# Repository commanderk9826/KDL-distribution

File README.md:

# Introduction

KDL(Kust Data Logger)는 대학생 자작자동차대회 출전차량을 위해 제작한 데이터로깅 플랫폼입니다. 
가이드에 따라 실시간 원격 모니터링, 데이터 분석 도구 등을 쉽게 이용할 수 있습니다.<br>

참여자 : 이채훈, 옹미령, 강호, 이지규<br>
PCB제작 : 고민제<br>
최신버전 [ui_config.json](https://github.com/commanderk9826/KDL-distribution/blob/main/ui_configKUST.json)

**주요 기능**
- CAN, 3축 가속도, GPS, 디지털/아날로그 신호 등 다양한 데이터 기록
- Micro SD 카드에 로그 저장
- 실시간 텔레메트리(원격 데이터 모니터링)
- 자체 시계(RTC)를 통한 실제 시간 추적
- 웹 기반 데이터 시각화 및 분석 도구

>**[가이드 문서](https://github.com/commanderk9826/KDL-distribution/wiki)**
>
>데이터로거 , 텔레메트리 모니터, 데이터 분석도구로 구성되어있습니다.

## 1. 데이터로거(KDL)

차량에 장착되어 데이터를 수집하는 장비입니다. 기록할 수 있는 데이터의 종류는

- CAN 2.0(A/B) 버스 트래픽
- 2채널 디지털 입력 신호
- 2채널 아날로그 입력 신호
- 3축 ±4g 가속도 (ADXL345)
- GPS 위치 정보 (NEO-7M)
- 전원(LV) 전압 및 자체 CPU 온도
- RTC 실제 시간 정보

<br>각 기능에 대한 설명은 [KDL가이드](https://github.com/commanderk9826/KDL-distribution/wiki/KDL-가이드)를 참고합니다.

## 2. 텔레메트리 모니터

데이터로거가 통신하는 텔레메트리 서버와, 실시간 데이터 모니터링을 위한 웹 클라이언트입니다.

### 서버
따로 설정하지 않는 한 데이터로거는 기본적으로 [commanderk.site](http://commanderk.site) 를 사용하여 데이터를 실시간으로 전송합니다.

> 기본 제공되는 텔레메트리 서버는 확인된 사용자만 이용할 수 있습니다.
>
> 별도의 비용은 없으며, lch9826@gmail.com 로 팀 이름, 사용할 차량 ID와 key를 보내 주시면 사용자 등록이 완료됩니다.

서버를 개별적으로 구축하고 싶다면 [서버 구축 가이드](https://github.com/commanderk9826/KDL-distribution/wiki/서버-구축-가이드)와 [웹 활용 가이드](https://github.com/commanderk9826/KDL-distribution/wiki/웹-활용-가이드)를 참고하여 직접 self-hosting할 수 있습니다.

### 클라이언트
실시간 모니터링 웹 클라이언트는 [https://commanderk.site/live](https://commanderk.site/live) 에서 제공됩니다.

각 사용자가 개별적으로 UI를 설정할 수 있으며, UI 설정 파일을 내보내고 불러오는 기능을 지원합니다.

자세한 사용법은 [클라이언트 사용 가이드](https://github.com/commanderk9826/KDL-distribution/wiki/클라이언트-사용-가이드)를 참고합니다.

## 데이터분석도구

데이터로거는 데이터를 정해진 [로그 프로토콜](https://github.com/commanderk9826/KDL-distribution/wiki/로그-프로토콜)에 따라 바이너리 파일로 SD 카드에 기록합니다.

이러한 로그를 사람이 읽을 수 있도록 json 및 csv 파일로 변환하는 해석기와, 데이터를 그래프로 시각화하는 분석 도구 모음입니다.

모두 웹 어플리케이션으로 구현되어 [https://www.commanderk.site](https://www.commanderk.site) 에서 바로 사용할 수 있습니다.

자세한 사용법은 [데이터 분석 도구 가이드](https://github.com/commanderk9826/KDL-distribution/wiki/데이터-분석-도구-가이드)를 참고합니다.

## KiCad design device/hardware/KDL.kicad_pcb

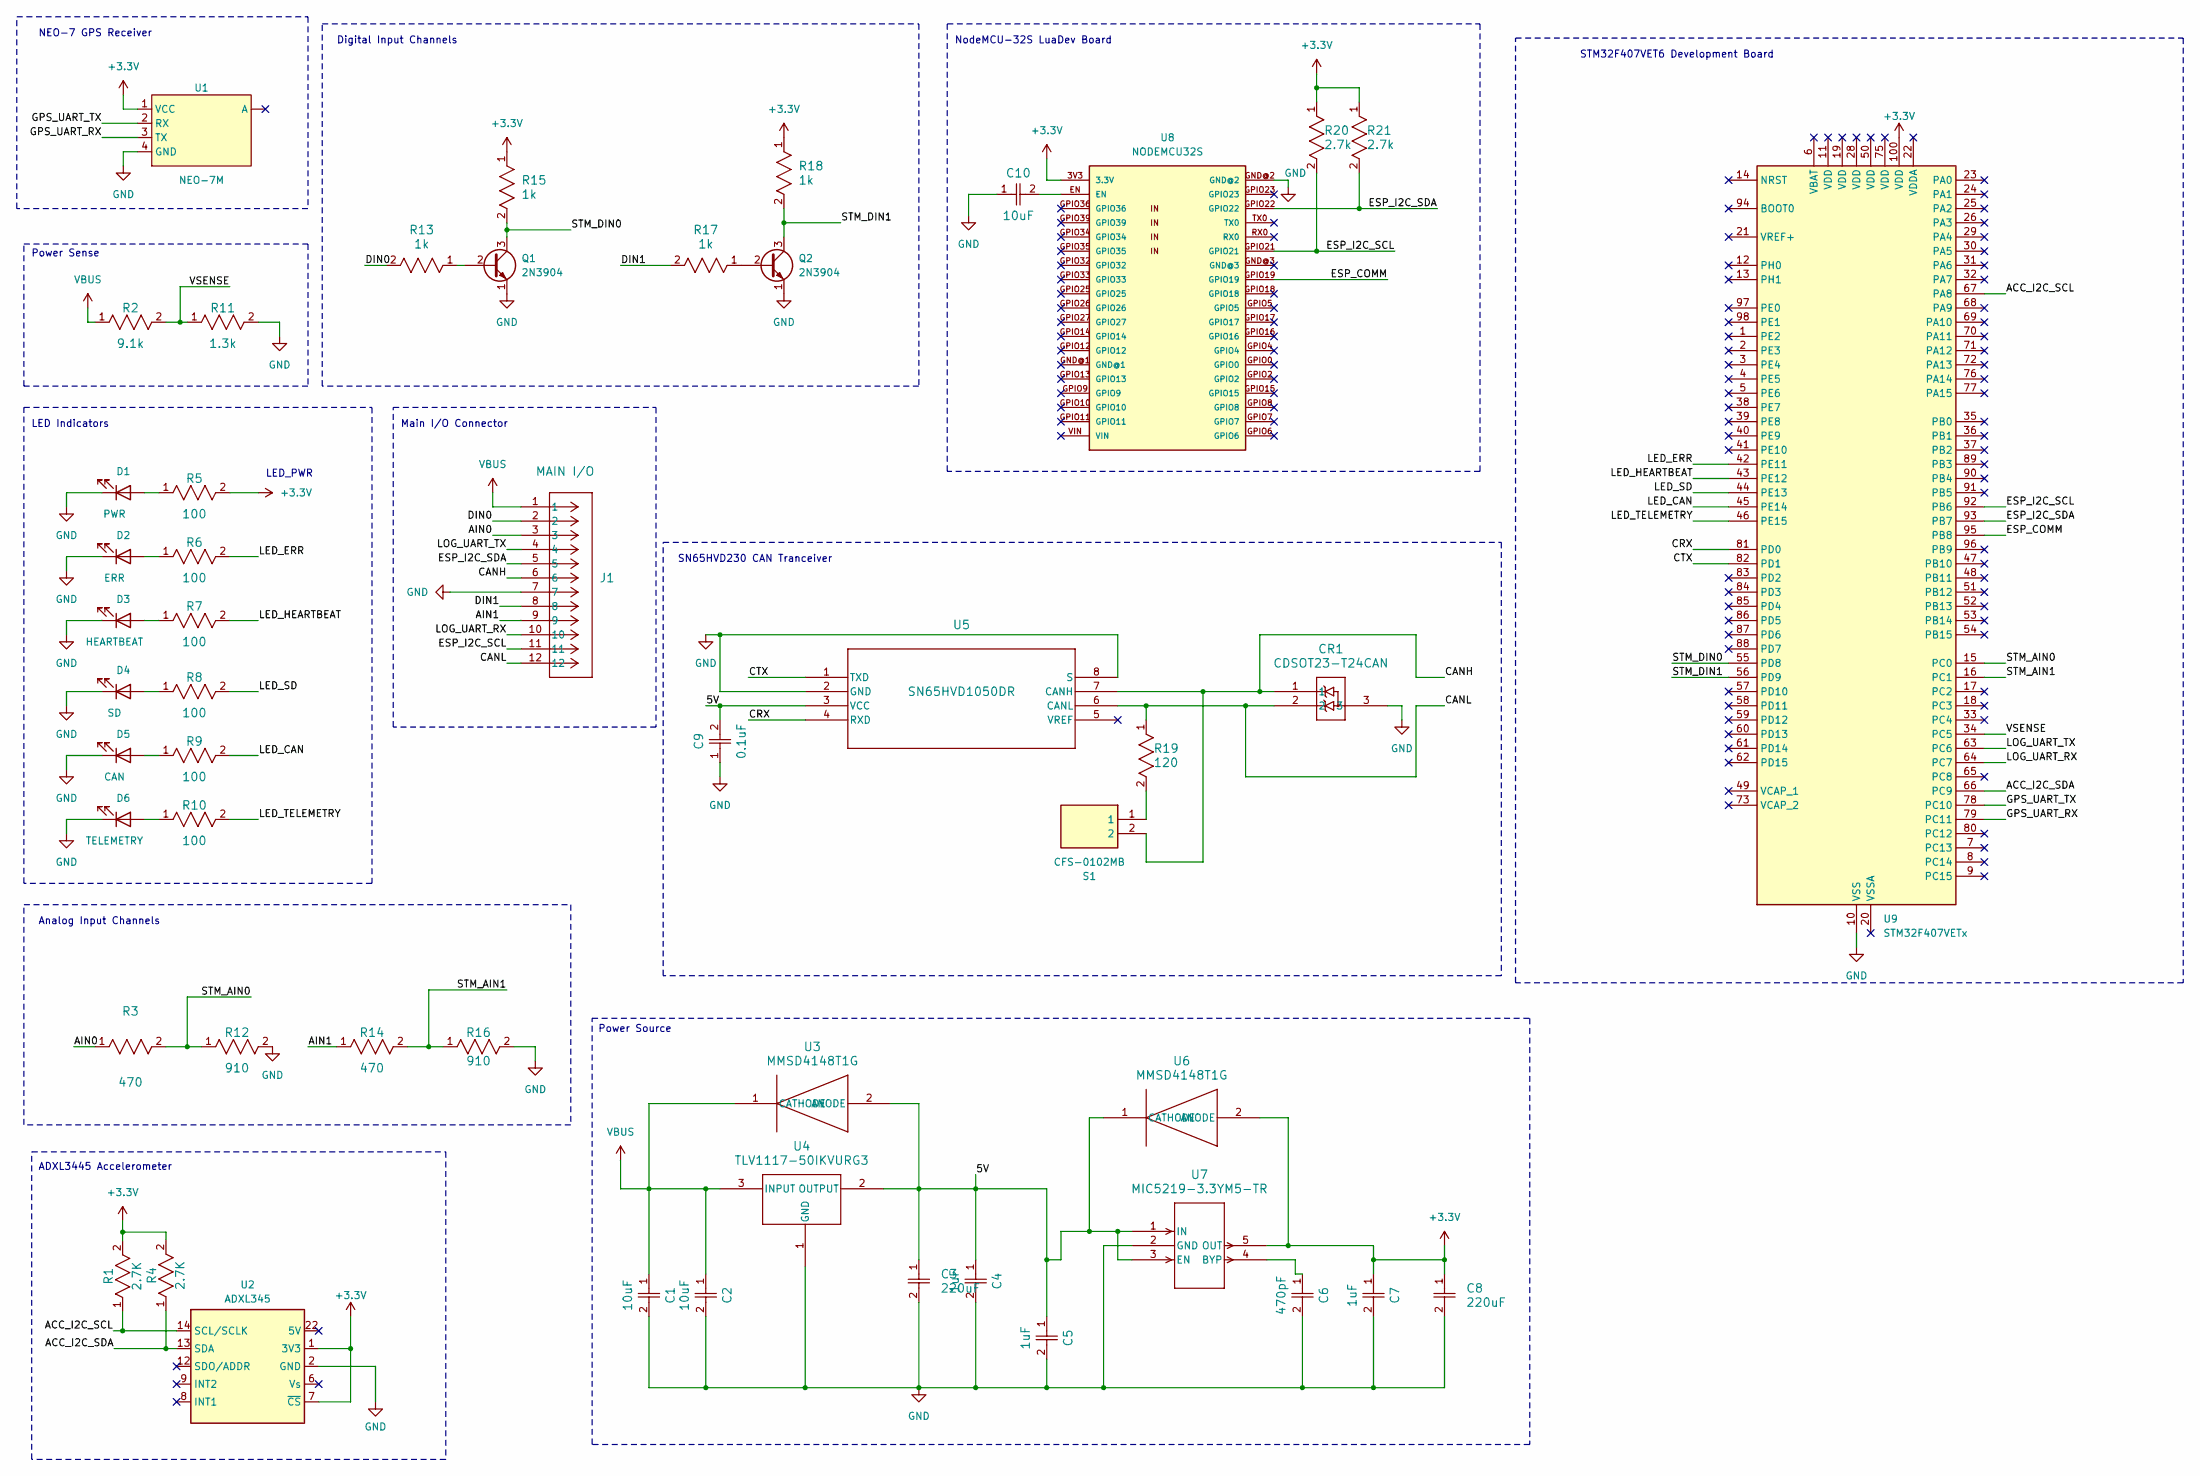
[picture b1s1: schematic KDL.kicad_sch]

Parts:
C1, C2, C10: 10uF; CAP_CL31_SAM
C3, C8: 220uF; CAP_ESK_E3_KEM
C4, C5, C7: 1uF; CAP_CL31_SAM
C6: 470pF; CAP_CL31_SAM
C9: 0.1uF; CAP_CL31_SAM
CR1: CDSOT23-T24CAN; SOT23-3L_STM
D1: PWR; LED_D3.0mm
D2: ERR; LED_D3.0mm
D3: HEARTBEAT; LED_D3.0mm
D4: SD; LED_D3.0mm
D5: CAN; LED_D3.0mm
D6: TELEMETRY; LED_D3.0mm
J1: MAIN I/O; CON_39301121
Q1, Q2: 2N3904; TO-92_Inline
R1, R4: 2.7K; RC1206N_YAG
R2: 9.1k; RC1206N_YAG
R3, R14: 470; RC1206N_YAG
R5, R6, R7, R8, R9, R10: 100; RC1206N_YAG
R11: 1.3k; RC1206N_YAG
R12, R16: 910; RC1206N_YAG
R13, R15, R17, R18: 1k; RC1206N_YAG
R19: 120; RC1206N_YAG
R20, R21: 2.7k; RC1206N_YAG
S1: CFS-0102MB; SOD10040X470N; Manufacturer_Part_Number CFS-0102MB
U1: NEO-7M; GPS_MODULE
U2: ADXL345; ADXL345_MODULE
U3, U6: MMSD4148T1G; SOD-123_ONS
U4: TLV1117-50IKVURG3; KVU3
U5: SN65HVD1050DR; D8
U7: MIC5219-3.3YM5-TR; SOT-23-5_M5_MCH
U8: NODEMCU32S
U9: STM32F407VETx; STM32F407_HOLDER

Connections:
+3.3V: C7.1, C8.1, R1.2, R4.2, R5.2, R15.1, R18.1, R20.1, R21.1, U1.1 (VCC), U2.1 (3V3), U2.7 (~CS), U6.2 (ANODE), U7.5 (OUT), U8.3V3 (3.3V), U9.100 (VDD)
/5V: C3.1, C4.1, C5.1, C9.2, U3.2 (ANODE), U4.2 (OUTPUT), U5.3 (VCC), U6.1 (CATHODE), U7.1 (IN), U7.3 (EN)
/ACC_I2C_SCL: R1.1, U2.14 (SCL/SCLK), U9.67 (PA8)
/ACC_I2C_SDA: R4.1, U2.13 (SDA), U9.66 (PC9)
/AIN0: J1.3, R3.1
/AIN1: J1.9, R14.1
/CANH: CR1.1, J1.6, S1.2, U5.7 (CANH)
/CANL: CR1.2, J1.12, R19.1, U5.6 (CANL)
/CRX: U5.4 (RXD), U9.81 (PD0)
/CTX: U5.1 (TXD), U9.82 (PD1)
/DIN0: J1.2, R13.2
/DIN1: J1.8, R17.2
/ESP_COMM: U8.GPIO19, U9.95 (PB8)
/ESP_I2C_SCL: J1.11, R20.2, U8.GPIO21, U9.92 (PB6)
/ESP_I2C_SDA: J1.5, R21.2, U8.GPIO22, U9.93 (PB7)
/GPS_UART_RX: U1.3 (TX), U9.79 (PC11)
/GPS_UART_TX: U1.2 (RX), U9.78 (PC10)
/LED_CAN: R9.2, U9.45 (PE14)
/LED_ERR: R6.2, U9.42 (PE11)
/LED_HEARTBEAT: R7.2, U9.43 (PE12)
/LED_SD: R8.2, U9.44 (PE13)
/LED_TELEMETRY: R10.2, U9.46 (PE15)
/LOG_UART_RX: J1.10, U9.64 (PC7)
/LOG_UART_TX: J1.4, U9.63 (PC6)
/STM_AIN0: R3.2, R12.1, U9.15 (PC0)
/STM_AIN1: R14.2, R16.1, U9.16 (PC1)
/STM_DIN0: Q1.3 (C), R15.2, U9.55 (PD8)
/STM_DIN1: Q2.3 (C), R18.2, U9.56 (PD9)
/VSENSE: R2.2, R11.1, U9.34 (PC5)
GND: C1.2, C2.2, C3.2, C4.2, C5.2, C6.2, C7.2, C8.2, C9.1, C10.1, CR1.3, D1.1 (K), D2.1 (K), D3.1 (K), D4.1 (K), D5.1 (K), D6.1 (K), J1.7, Q1.1 (E), Q2.1 (E), R11.2, R12.2, R16.2, U1.4 (GND), U2.2 (GND), U4.1 (GND), U5.2 (GND), U5.8 (S), U7.2 (GND), U8.GND@2, U9.10 (VSS), U9.27 (VSS), U9.74 (VSS), U9.99 (VSS)
unnamed: C10.2, U8.EN
unnamed: D1.2 (A), R5.1
unnamed: D2.2 (A), R6.1
unnamed: D3.2 (A), R7.1
unnamed: D4.2 (A), R8.1
unnamed: D5.2 (A), R9.1
unnamed: D6.2 (A), R10.1
unnamed: Q1.2 (B), R13.1
unnamed: Q2.2 (B), R17.1
unnamed: R19.2, S1.1
unnamed: C6.1, U7.4 (BYP)
VBUS: C1.1, C2.1, J1.1, R2.1, U3.1 (CATHODE), U4.3 (INPUT)

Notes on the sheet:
Power Source
Analog Input Channels
NodeMCU-32S LuaDev Board
LED_PWR
Main I/O Connector
ADXL3445 Accelerometer
NEO-7 GPS Receiver
Digital Input Channels
LED Indicators
STM32F407VET6 Development Board
Power Sense
SN65HVD230 CAN Tranceiver

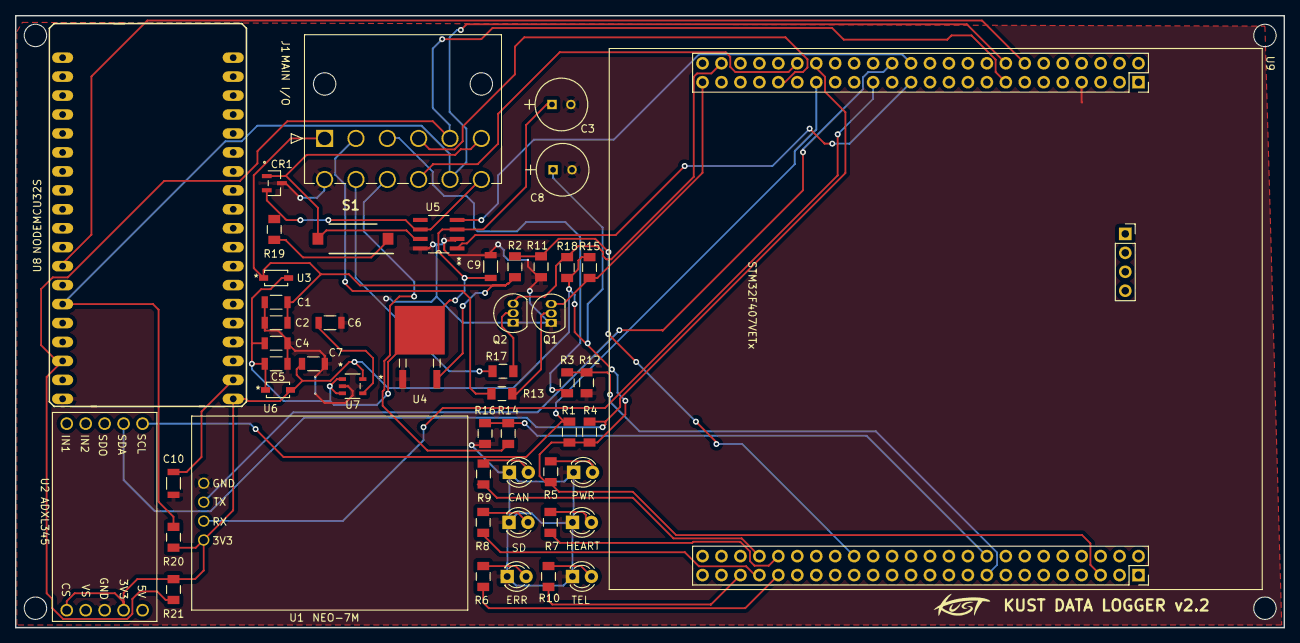
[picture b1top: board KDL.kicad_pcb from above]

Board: 2 copper layers, 170.0 x 82.0 mm, 51 parts (0 on the bottom side), 42 nets.

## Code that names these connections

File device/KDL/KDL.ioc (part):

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Mcu.Name=STM32F407V(E-G)Tx
Mcu.Package=LQFP100
Mcu.UserName=STM32F407VETx
PA10.GPIOParameters=GPIO_Label
PA10.GPIO_Label=USART_DEBUG_RX
PA10.Mode=Asynchronous
PA10.Signal=USART1_RX
PA6.GPIOParameters=GPIO_PuPd,GPIO_Label
PA6.GPIO_Label=LED_ONBOARD_0
PA6.GPIO_PuPd=GPIO_PULLDOWN
PA6.Signal=GPIO_Output
PA7.GPIOParameters=GPIO_PuPd,GPIO_Label
PA7.GPIO_Label=LED_ONBOARD_1
PA7.GPIO_PuPd=GPIO_PULLDOWN
PA7.Signal=GPIO_Output
PA8.GPIOParameters=GPIO_Label
PA8.GPIO_Label=I2C_ACC_SCL
PA8.Mode=I2C
PA8.Signal=I2C3_SCL
PA9.GPIOParameters=GPIO_Label
PA9.GPIO_Label=USART_DEBUG_TX
PA9.Mode=Asynchronous
PA9.Signal=USART1_TX
PB12.GPIOParameters=GPIO_PuPd,GPIO_Label
PB12.GPIO_Label=SDIO_DETECT
PB12.GPIO_PuPd=GPIO_PULLDOWN
PB12.Signal=GPIO_Input
PB6.GPIOParameters=GPIO_Label
PB6.GPIO_Label=I2C_ESP_SCL
PB6.Mode=I2C
PB6.Signal=I2C1_SCL
PB7.GPIOParameters=GPIO_Label
PB7.GPIO_Label=I2C_ESP_SDA
PB7.Mode=I2C
PB7.Signal=I2C1_SDA
PB8.GPIOParameters=GPIO_Label,GPIO_ModeDefaultEXTI
PB8.GPIO_Label=ESP_COMM
PB8.GPIO_ModeDefaultEXTI=GPIO_MODE_IT_RISING_FALLING
PB8.Signal=GPXTI8
PC0.GPIOParameters=GPIO_Label
PC0.GPIO_Label=AIN0
PC0.Signal=ADCx_IN10
PC1.GPIOParameters=GPIO_Label
PC1.GPIO_Label=AIN1
PC1.Signal=ADCx_IN11
PC10.GPIOParameters=GPIO_Label
PC10.GPIO_Label=USART_GPS_TX
PC10.Mode=Asynchronous
PC10.Signal=USART3_TX
PC11.GPIOParameters=GPIO_Label
PC11.GPIO_Label=USART_GPS_RX
PC11.Mode=Asynchronous
PC11.Signal=USART3_RX
PC12.Mode=SD_1_bit
PC12.Signal=SDIO_CK
PC14-OSC32_IN.Mode=LSE-External-Oscillator
PC14-OSC32_IN.Signal=RCC_OSC32_IN
PC15-OSC32_OUT.Mode=LSE-External-Oscillator
PC15-OSC32_OUT.Signal=RCC_OSC32_OUT
PC5.GPIOParameters=GPIO_Label
PC5.GPIO_Label=Vsense
PC5.Signal=ADCx_IN15
PC6.GPIOParameters=GPIO_Label
PC6.GPIO_Label=USART_LOG_TX
PC6.Mode=Asynchronous
PC6.Signal=USART6_TX
PC7.GPIOParameters=GPIO_Label
PC7.GPIO_Label=USART_LOG_RX
PC7.Mode=Asynchronous
PC7.Signal=USART6_RX
PC8.GPIOParameters=GPIO_PuPd
PC8.GPIO_PuPd=GPIO_PULLUP
PC8.Mode=SD_1_bit
PC8.Signal=SDIO_D0
PC9.GPIOParameters=GPIO_Label
PC9.GPIO_Label=I2C_ACC_SDA
PC9.Mode=I2C
PC9.Signal=I2C3_SDA
PD0.Mode=CAN_Activate
PD0.Signal=CAN1_RX
PD1.Mode=CAN_Activate
PD1.Signal=CAN1_TX
PD2.GPIOParameters=GPIO_PuPd
PD2.GPIO_PuPd=GPIO_PULLUP
PD2.Mode=SD_1_bit
PD2.Signal=SDIO_CMD
PD8.GPIOParameters=GPIO_PuPd,GPIO_Label
PD8.GPIO_Label=DIN0
PD8.GPIO_PuPd=GPIO_PULLDOWN
PD8.Signal=GPIO_Input
PD9.GPIOParameters=GPIO_PuPd,GPIO_Label
PD9.GPIO_Label=DIN1
PD9.GPIO_PuPd=GPIO_PULLDOWN
PD9.Signal=GPIO_Input
PE10.GPIOParameters=GPIO_Label
PE10.GPIO_Label=LED_CUSTOM_1
PE10.Signal=GPIO_Output
PE11.GPIOParameters=GPIO_Label
PE11.GPIO_Label=LED_ERR
PE11.Signal=GPIO_Output
PE12.GPIOParameters=GPIO_Label
PE12.GPIO_Label=LED_HEARTBEAT
PE12.Signal=GPIO_Output
PE13.GPIOParameters=GPIO_Label
PE13.GPIO_Label=LED_SD
PE13.Signal=GPIO_Output
PE14.GPIOParameters=GPIO_Label
PE14.GPIO_Label=LED_CAN
PE14.Signal=GPIO_Output
PE15.GPIOParameters=GPIO_Label
PE15.GPIO_Label=LED_TELEMETRY
PE15.Signal=GPIO_Output
PE9.GPIOParameters=GPIO_Label
PE9.GPIO_Label=LED_CUSTOM_0
PE9.Signal=GPIO_Output
PH0-OSC_IN.Mode=HSE-External-Oscillator
PH0-OSC_IN.Signal=RCC_OSC_IN
PH1-OSC_OUT.Mode=HSE-External-Oscillator
PH1-OSC_OUT.Signal=RCC_OSC_OUT
RCC.HSE_VALUE=8000000
RCC.SYSCLKFreq_VALUE=168000000
RCC.SYSCLKSource=RCC_SYSCLKSOURCE_PLLCLK
board=custom

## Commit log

2024-05-14 add server folder
2024-05-14 add web
2024-05-14 add device
2024-05-14 add telemetry
2024-05-15 add Readme1
2024-05-15 add Readme2
2024-05-26 add device ver2.2
2024-07-03 2024.07.03
2024-07-03 add ESP32
2024-07-04 add PCBguide
2024-07-04 add Introduction
2024-07-04 finish Readme
2024-07-04 update ui on readme
2024-07-04 update ui on readme2
2024-07-05 edit image
2024-07-05 edit image size
2024-07-06 modi readme image size
2024-07-10 add ui, protocol
2024-07-10 240711
2024-07-15 add 240715
2024-09-04 2024.09.04
2024-09-12 24.09.12
2024-11-18 24.11.18
